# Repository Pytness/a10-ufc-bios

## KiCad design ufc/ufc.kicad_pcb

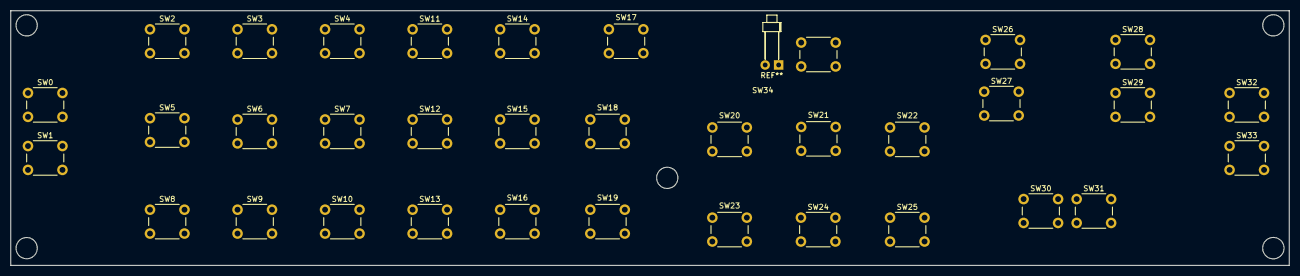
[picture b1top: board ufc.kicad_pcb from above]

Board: 2 copper layers, 241.0 x 48.0 mm, 35 parts (0 on the bottom side), 3 nets, no tracks yet.

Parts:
SW0, SW1, SW2, SW3, SW4, SW5, SW6, SW7, SW8, SW9, SW10, SW11, SW12, SW13, SW14, SW15, SW16, SW17, SW18, SW19, SW20, SW21, SW22, SW23, SW24, SW25, SW26, SW27, SW28, SW29, SW30, SW31, SW32, SW33, SW34: SW_MEC_5E; SW_PUSH_6mm

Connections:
/R0: SW0.1, SW1.1, SW2.1, SW3.1, SW4.1, SW5.1, SW6.1, SW7.1, SW8.1, SW9.1, SW10.1, SW11.1, SW12.1, SW13.1, SW14.1, SW15.1
/R1: SW16.1, SW17.1, SW18.1, SW19.1, SW20.1, SW21.1, SW22.1, SW23.1, SW24.1, SW25.1, SW26.1, SW27.1, SW28.1, SW29.1, SW30.1, SW31.1
/R2: SW32.1, SW33.1

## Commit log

2024-06-25 Change formatting
2024-06-25 Remove useless comments
2024-06-25 Minor refactor of read_buttons function
2024-06-25 Fix incorrect syntax. Thank you BISECT
2024-06-25 Change columns starting address
2024-06-25 Add row/col discover function
2024-06-25 Add support for multi col/row expanders
2024-06-25 Fix read_buttons not exiting when button press is found
2024-06-25 Fix incorrect row chunk button index calculation
2024-06-25 Minor refactoring and declaration moving
2024-06-26 Use lcd to show alphanum
2024-06-27 Add partial implementation for multi button press
2024-06-28 Move into platformio project
2024-07-01 Add joystick library
2024-07-01 Minor var naming change
2024-07-11 Disable line length limit in clang format
2024-07-11 Add dcs bios library
2024-07-11 Add properties for dcs button handling
2024-07-11 Add dcs a10c buttons json
2024-07-11 Move previous main to temp file
2024-07-11 Use basic dcs bios main
2024-07-11 Adapt previous code to work with dcs-bios
2024-07-11 Remove redundant comment
2024-07-12 Add ufc kicad pcb
2024-11-05 Auto-commit by script
